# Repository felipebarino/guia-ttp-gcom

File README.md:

# Guia de uso - TTP Proto1s

<p align="center">
  
  <br>
  <strong>Grupo de Controle e Modelagem</strong>
</p>

# Guia de uso - TTP Proto1s

Este é um guia rápido e repositório de informações para fabricação de PCBs utilizando a fresadora TTP Proto 1S.

## Aviso de Referência e Complementaridade

Este site é um guia prático interno do laboratório e destina-se a padronizar o fluxo de trabalho e registrar as regras de projeto da nossa bancada. **Este material complementa e NÃO substitui o manual/tutorial oficial** fornecido pela TTP Indústria Mecânica Ltda. Ele pode ser acessado em [Tutorial TTP](https://www.ttp.ind.br/portal/tutorial/index.html).

## Objetivo

O objetivo principal é garantir uma boa qualidade de prototipagem com o mínimo de iterações possíveis, assegurando o bom uso dos recursos e a qualidade final do protótipo. Para tal, o site contém um guia prático para prototipagem eletrônica utilizando as ferramentas disponíveis no GCOM. Aqui se encontra regras de projeto, boas práticas e procedimentos de manufatura que auxiliam no comprimento deste objetivo principal. 

## TODO

- [ ] Descrever melhor o fluxo dentro do CAM

- [ ] Gravar o fluxo completo no CAM e publicar no YouTube

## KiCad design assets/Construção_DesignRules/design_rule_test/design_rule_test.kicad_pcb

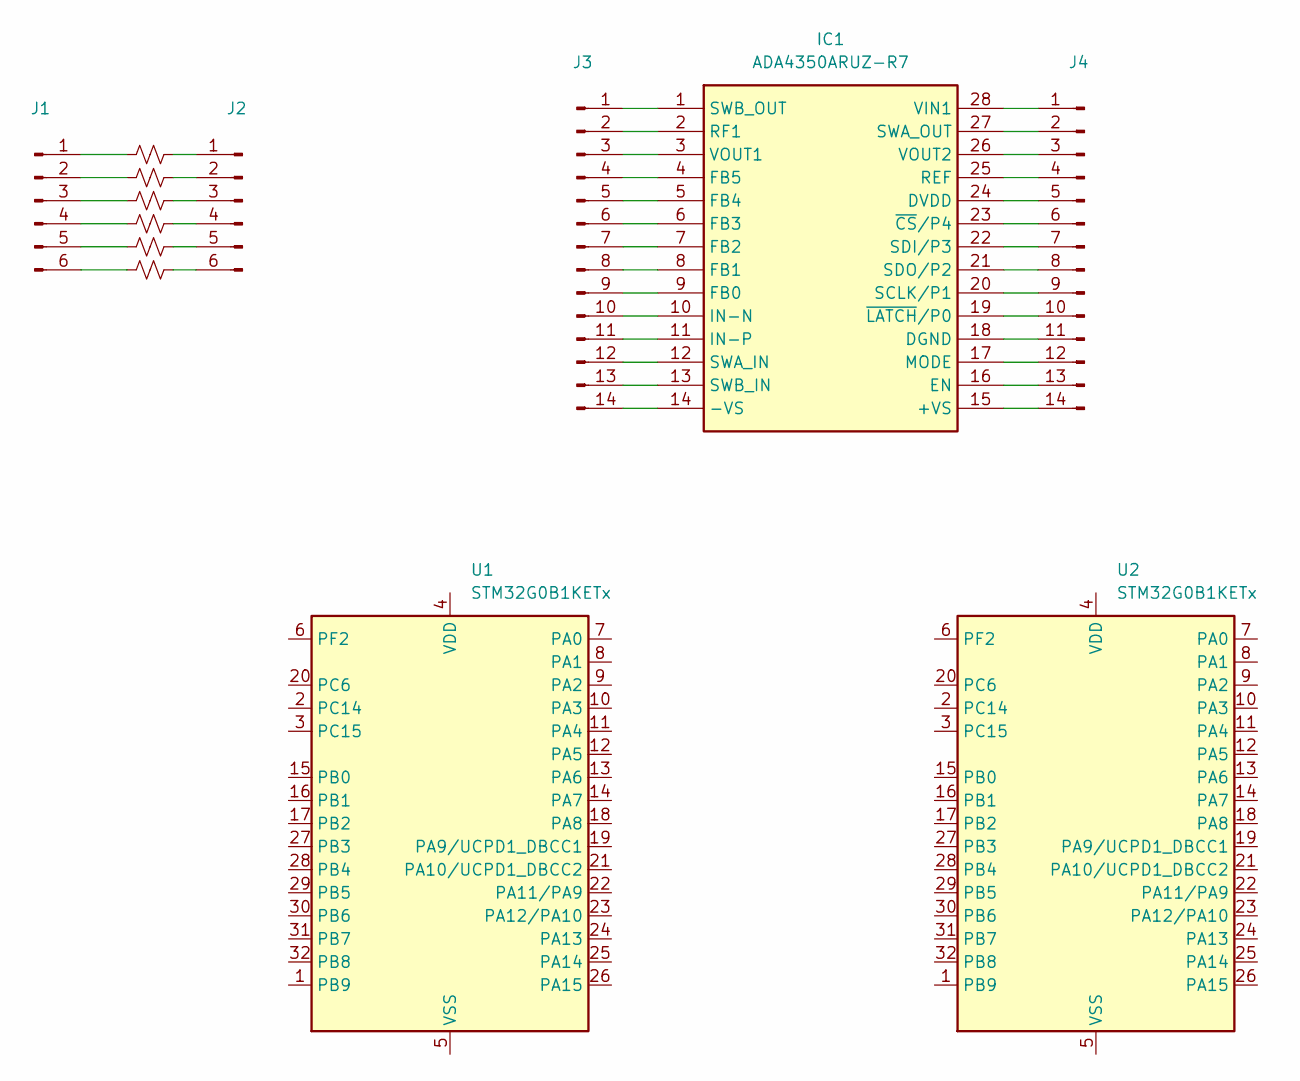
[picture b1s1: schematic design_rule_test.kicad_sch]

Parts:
IC1: ADA4350ARUZ-R7; SOP65P640X120-28N; Manufacturer_Part_Number ADA4350ARUZ-R7; Mouser Part Number 584-ADA4350ARUZ-R7
J1, J2: Conn_01x06_Pin; PinHeader_1x06_P2.54mm_Vertical
J3, J4: Conn_01x14_Pin; PinHeader_1x14_P2.54mm_Vertical
R1, R2, R3, R4, R5, R6: R_Small_US; R_0805_2012Metric_Pad1.20x1.40mm_HandSolder
U1, U2: STM32G0B1KETx; LQFP-32_7x7mm_P0.8mm

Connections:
unnamed: IC1.15 (+VS), J4.14
unnamed: IC1.14 (-VS), J3.14
unnamed: IC1.18 (DGND), J4.11
unnamed: IC1.24 (DVDD), J4.5
unnamed: IC1.16 (EN), J4.13
unnamed: IC1.9 (FB0), J3.9
unnamed: IC1.8 (FB1), J3.8
unnamed: IC1.7 (FB2), J3.7
unnamed: IC1.6 (FB3), J3.6
unnamed: IC1.5 (FB4), J3.5
unnamed: IC1.4 (FB5), J3.4
unnamed: IC1.10 (IN-N), J3.10
unnamed: IC1.11 (IN-P), J3.11
unnamed: IC1.17 (MODE), J4.12
unnamed: IC1.25 (REF), J4.4
unnamed: IC1.2 (RF1), J3.2
unnamed: IC1.20 (SCLK/P1), J4.9
unnamed: IC1.22 (SDI/P3), J4.7
unnamed: IC1.21 (SDO/P2), J4.8
unnamed: IC1.12 (SWA_IN), J3.12
unnamed: IC1.27 (SWA_OUT), J4.2
unnamed: IC1.13 (SWB_IN), J3.13
unnamed: IC1.1 (SWB_OUT), J3.1
unnamed: IC1.28 (VIN1), J4.1
unnamed: IC1.3 (VOUT1), J3.3
unnamed: IC1.26 (VOUT2), J4.3
unnamed: IC1.23 (~CS/P4), J4.6
unnamed: IC1.19 (~LATCH/P0), J4.10
unnamed: J1.1, R1.1
unnamed: J1.2, R2.1
unnamed: J1.3, R3.1
unnamed: J1.4, R4.1
unnamed: J1.5, R5.1
unnamed: J1.6, R6.1
unnamed: J2.1, R1.2
unnamed: J2.2, R2.2
unnamed: J2.3, R3.2
unnamed: J2.4, R4.2
unnamed: J2.5, R5.2
unnamed: J2.6, R6.2

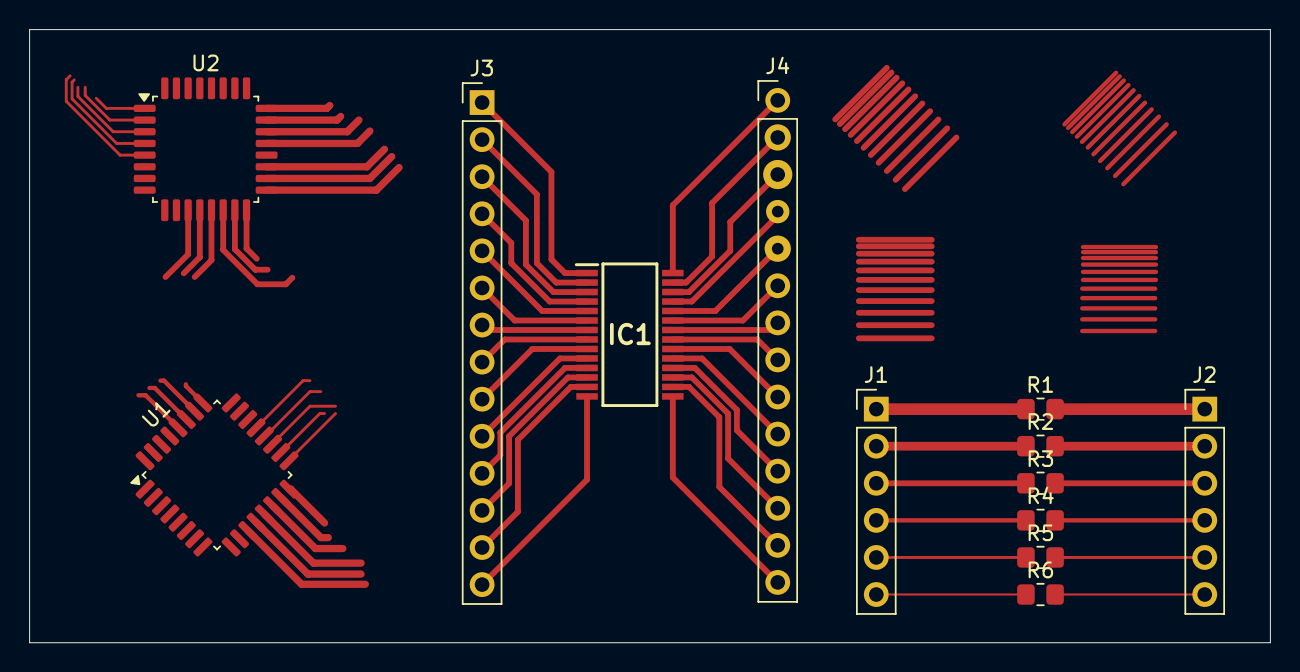
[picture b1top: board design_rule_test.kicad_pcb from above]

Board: 2 copper layers, 85.0 x 42.0 mm, 13 parts (0 on the bottom side), 40 nets.
